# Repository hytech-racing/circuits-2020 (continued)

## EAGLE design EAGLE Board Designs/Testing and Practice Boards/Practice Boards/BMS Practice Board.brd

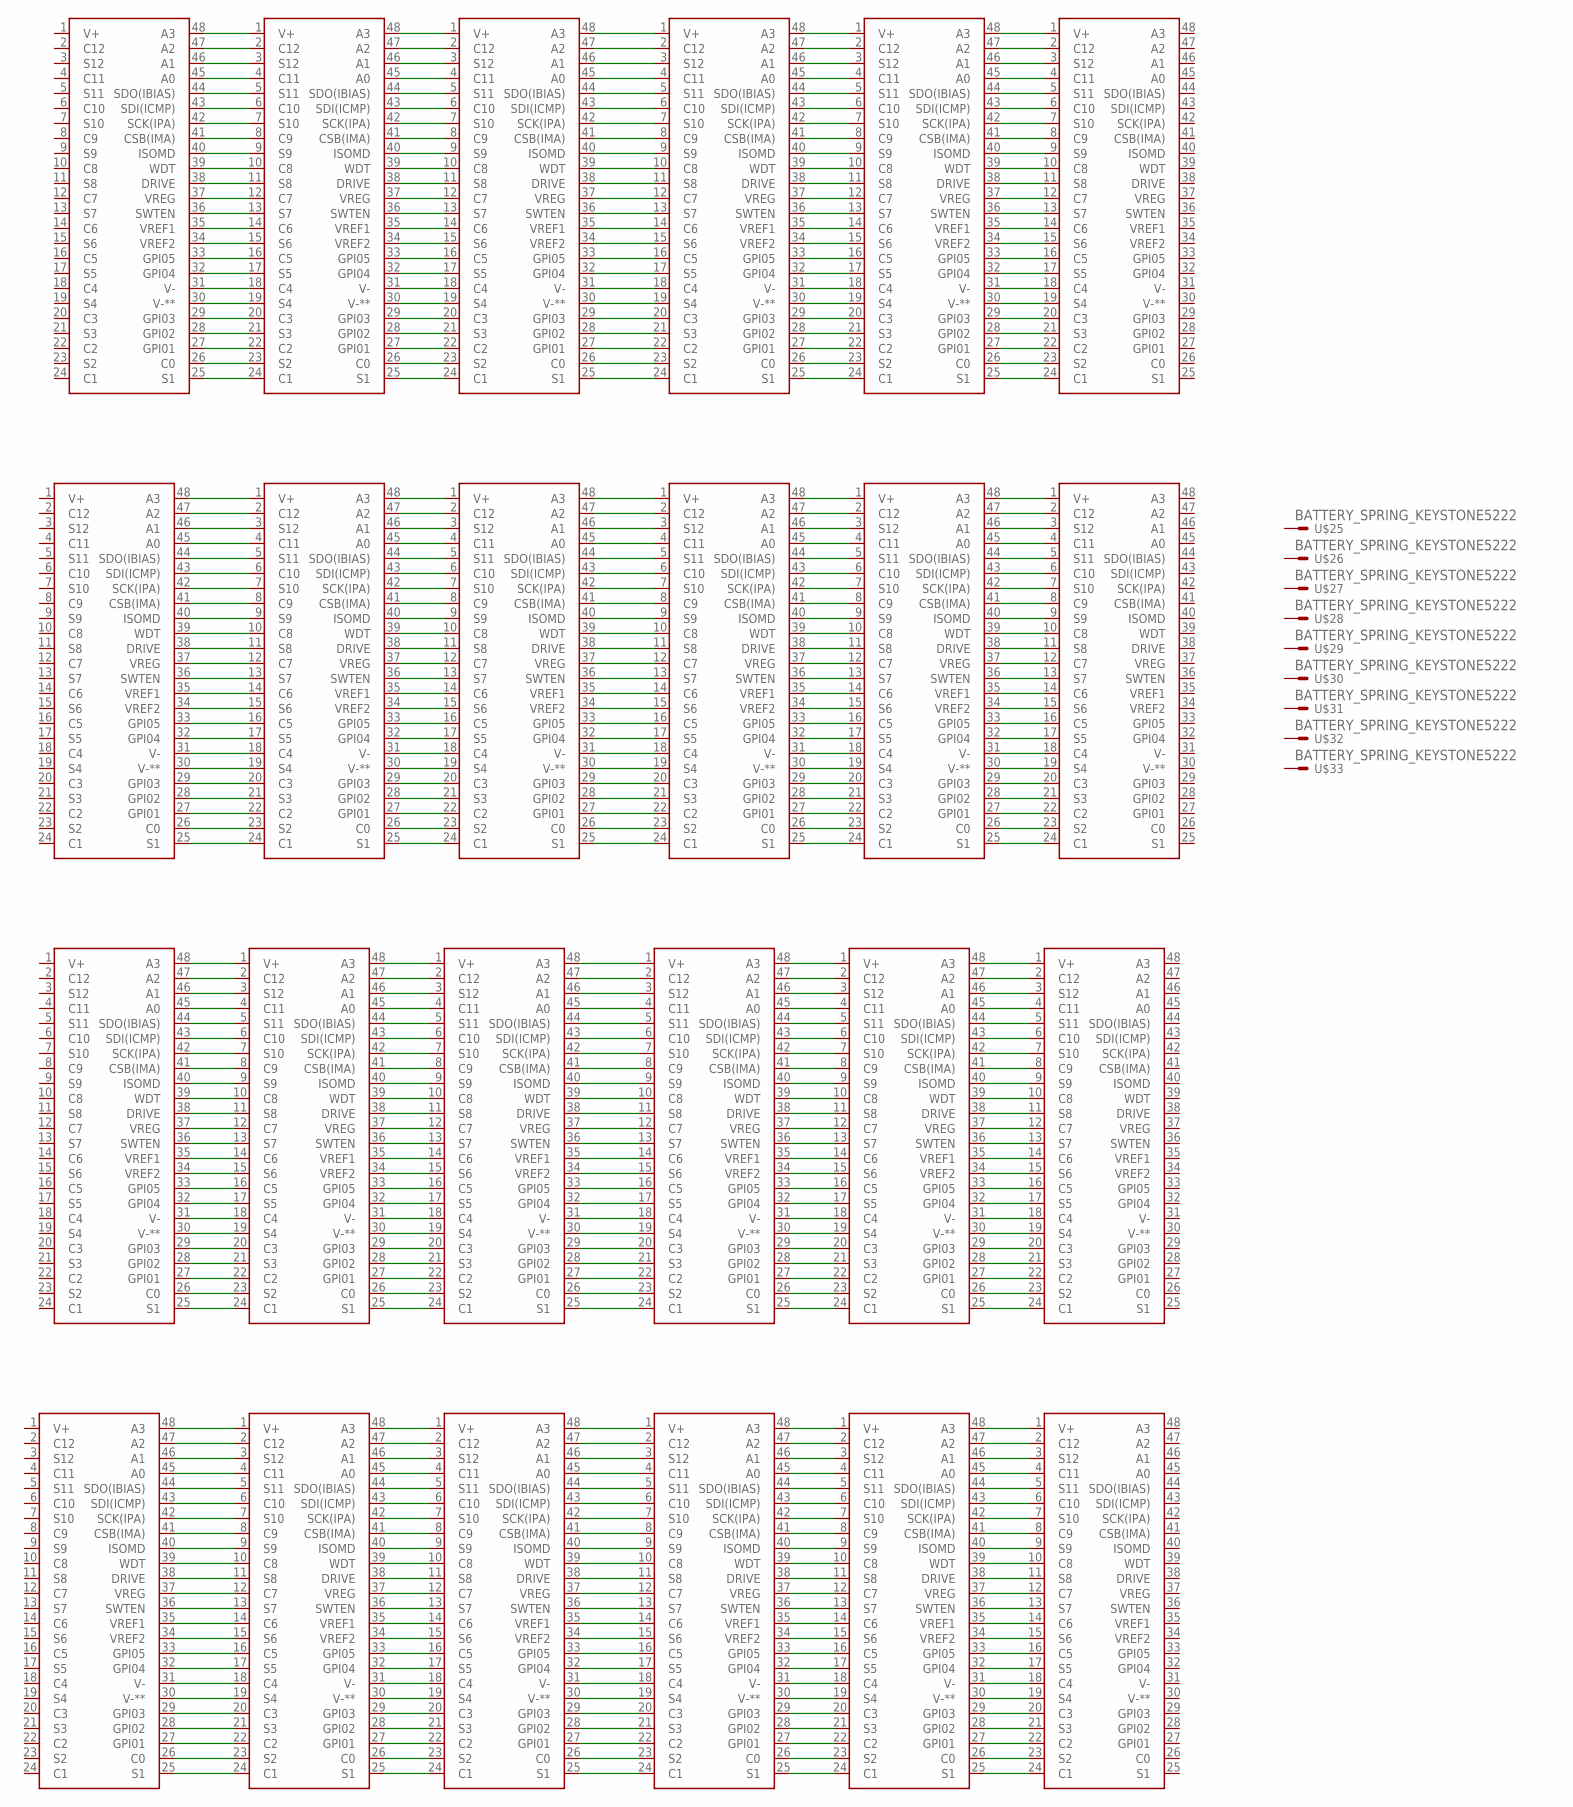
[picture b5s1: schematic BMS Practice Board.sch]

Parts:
U$1, U$2, U$3, U$4, U$5, U$6, U$7, U$8, U$9, U$10, U$11, U$12, U$13, U$14, U$15, U$16, U$17, U$18, U$19, U$20, U$21, U$22, U$23, U$24: LTC6804-2; LTC6804
U$25, U$26, U$27, U$28, U$29, U$30, U$31, U$32, U$33: BATTERY_SPRING_KEYSTONE5222; KEYSTONE5222

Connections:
unnamed: U$1.48 (A3), U$2.1 (V+)
unnamed: U$1.47 (A2), U$2.2 (C12)
unnamed: U$1.46 (A1), U$2.3 (S12)
unnamed: U$1.45 (A0), U$2.4 (C11)
unnamed: U$1.44 (SDO(IBIAS)), U$2.5 (S11)
unnamed: U$1.43 (SDI(ICMP)), U$2.6 (C10)
unnamed: U$1.42 (SCK(IPA)), U$2.7 (S10)
unnamed: U$1.41 (CSB(IMA)), U$2.8 (C9)
unnamed: U$1.40 (ISOMD), U$2.9 (S9)
unnamed: U$1.39 (WDT), U$2.10 (C8)
unnamed: U$1.38 (DRIVE), U$2.11 (S8)
unnamed: U$1.37 (VREG), U$2.12 (C7)
unnamed: U$1.36 (SWTEN), U$2.13 (S7)
unnamed: U$1.35 (VREF1), U$2.14 (C6)
unnamed: U$1.34 (VREF2), U$2.15 (S6)
unnamed: U$1.33 (GPI05), U$2.16 (C5)
unnamed: U$1.32 (GPI04), U$2.17 (S5)
unnamed: U$1.31 (V-), U$2.18 (C4)
unnamed: U$1.30 (V-**), U$2.19 (S4)
unnamed: U$1.29 (GPI03), U$2.20 (C3)
unnamed: U$1.28 (GPI02), U$2.21 (S3)
unnamed: U$1.27 (GPI01), U$2.22 (C2)
unnamed: U$1.26 (C0), U$2.23 (S2)
unnamed: U$1.25 (S1), U$2.24 (C1)
unnamed: U$2.48 (A3), U$3.1 (V+)
unnamed: U$2.47 (A2), U$3.2 (C12)
unnamed: U$2.46 (A1), U$3.3 (S12)
unnamed: U$2.45 (A0), U$3.4 (C11)
unnamed: U$2.44 (SDO(IBIAS)), U$3.5 (S11)
unnamed: U$2.43 (SDI(ICMP)), U$3.6 (C10)
unnamed: U$2.42 (SCK(IPA)), U$3.7 (S10)
unnamed: U$2.41 (CSB(IMA)), U$3.8 (C9)
unnamed: U$2.40 (ISOMD), U$3.9 (S9)
unnamed: U$2.39 (WDT), U$3.10 (C8)
unnamed: U$2.38 (DRIVE), U$3.11 (S8)
unnamed: U$2.37 (VREG), U$3.12 (C7)
unnamed: U$2.36 (SWTEN), U$3.13 (S7)
unnamed: U$2.35 (VREF1), U$3.14 (C6)
unnamed: U$2.34 (VREF2), U$3.15 (S6)
unnamed: U$2.33 (GPI05), U$3.16 (C5)
unnamed: U$2.32 (GPI04), U$3.17 (S5)
unnamed: U$2.31 (V-), U$3.18 (C4)
unnamed: U$2.30 (V-**), U$3.19 (S4)
unnamed: U$2.29 (GPI03), U$3.20 (C3)
unnamed: U$2.28 (GPI02), U$3.21 (S3)
unnamed: U$2.27 (GPI01), U$3.22 (C2)
unnamed: U$2.26 (C0), U$3.23 (S2)
unnamed: U$2.25 (S1), U$3.24 (C1)
unnamed: U$3.48 (A3), U$4.1 (V+)
unnamed: U$3.47 (A2), U$4.2 (C12)
unnamed: U$3.46 (A1), U$4.3 (S12)
unnamed: U$3.45 (A0), U$4.4 (C11)
unnamed: U$3.44 (SDO(IBIAS)), U$4.5 (S11)
unnamed: U$3.43 (SDI(ICMP)), U$4.6 (C10)
unnamed: U$3.42 (SCK(IPA)), U$4.7 (S10)
unnamed: U$3.41 (CSB(IMA)), U$4.8 (C9)
unnamed: U$3.40 (ISOMD), U$4.9 (S9)
unnamed: U$3.39 (WDT), U$4.10 (C8)
unnamed: U$3.38 (DRIVE), U$4.11 (S8)
unnamed: U$3.37 (VREG), U$4.12 (C7)
unnamed: U$3.36 (SWTEN), U$4.13 (S7)
unnamed: U$3.35 (VREF1), U$4.14 (C6)
unnamed: U$3.34 (VREF2), U$4.15 (S6)
unnamed: U$3.33 (GPI05), U$4.16 (C5)
unnamed: U$3.32 (GPI04), U$4.17 (S5)
unnamed: U$3.31 (V-), U$4.18 (C4)
unnamed: U$3.30 (V-**), U$4.19 (S4)
unnamed: U$3.29 (GPI03), U$4.20 (C3)
unnamed: U$3.28 (GPI02), U$4.21 (S3)
unnamed: U$3.27 (GPI01), U$4.22 (C2)
unnamed: U$3.26 (C0), U$4.23 (S2)
unnamed: U$3.25 (S1), U$4.24 (C1)
unnamed: U$4.48 (A3), U$5.1 (V+)
unnamed: U$4.47 (A2), U$5.2 (C12)
unnamed: U$4.46 (A1), U$5.3 (S12)
unnamed: U$4.45 (A0), U$5.4 (C11)
unnamed: U$4.44 (SDO(IBIAS)), U$5.5 (S11)
unnamed: U$4.43 (SDI(ICMP)), U$5.6 (C10)
unnamed: U$4.42 (SCK(IPA)), U$5.7 (S10)
unnamed: U$4.41 (CSB(IMA)), U$5.8 (C9)
unnamed: U$4.40 (ISOMD), U$5.9 (S9)
unnamed: U$4.39 (WDT), U$5.10 (C8)
unnamed: U$4.38 (DRIVE), U$5.11 (S8)
unnamed: U$4.37 (VREG), U$5.12 (C7)
unnamed: U$4.36 (SWTEN), U$5.13 (S7)
unnamed: U$4.35 (VREF1), U$5.14 (C6)
unnamed: U$4.34 (VREF2), U$5.15 (S6)
unnamed: U$4.33 (GPI05), U$5.16 (C5)
unnamed: U$4.32 (GPI04), U$5.17 (S5)
unnamed: U$4.31 (V-), U$5.18 (C4)
unnamed: U$4.30 (V-**), U$5.19 (S4)
unnamed: U$4.29 (GPI03), U$5.20 (C3)
unnamed: U$4.28 (GPI02), U$5.21 (S3)
unnamed: U$4.27 (GPI01), U$5.22 (C2)
unnamed: U$4.26 (C0), U$5.23 (S2)
unnamed: U$4.25 (S1), U$5.24 (C1)
unnamed: U$5.48 (A3), U$6.1 (V+)
unnamed: U$5.47 (A2), U$6.2 (C12)
unnamed: U$5.46 (A1), U$6.3 (S12)
unnamed: U$5.45 (A0), U$6.4 (C11)
unnamed: U$5.44 (SDO(IBIAS)), U$6.5 (S11)
unnamed: U$5.43 (SDI(ICMP)), U$6.6 (C10)
unnamed: U$5.42 (SCK(IPA)), U$6.7 (S10)
unnamed: U$5.41 (CSB(IMA)), U$6.8 (C9)
unnamed: U$5.40 (ISOMD), U$6.9 (S9)
unnamed: U$5.39 (WDT), U$6.10 (C8)
unnamed: U$5.38 (DRIVE), U$6.11 (S8)
unnamed: U$5.37 (VREG), U$6.12 (C7)
unnamed: U$5.36 (SWTEN), U$6.13 (S7)
unnamed: U$5.35 (VREF1), U$6.14 (C6)
unnamed: U$5.34 (VREF2), U$6.15 (S6)
unnamed: U$5.33 (GPI05), U$6.16 (C5)
unnamed: U$5.32 (GPI04), U$6.17 (S5)
unnamed: U$5.31 (V-), U$6.18 (C4)
unnamed: U$5.30 (V-**), U$6.19 (S4)
unnamed: U$5.29 (GPI03), U$6.20 (C3)
unnamed: U$5.28 (GPI02), U$6.21 (S3)
unnamed: U$5.27 (GPI01), U$6.22 (C2)
unnamed: U$5.26 (C0), U$6.23 (S2)
unnamed: U$5.25 (S1), U$6.24 (C1)
unnamed: U$7.25 (S1), U$8.24 (C1)
unnamed: U$7.26 (C0), U$8.23 (S2)
unnamed: U$7.27 (GPI01), U$8.22 (C2)
unnamed: U$7.28 (GPI02), U$8.21 (S3)
unnamed: U$7.29 (GPI03), U$8.20 (C3)
unnamed: U$7.30 (V-**), U$8.19 (S4)
unnamed: U$7.31 (V-), U$8.18 (C4)
unnamed: U$7.32 (GPI04), U$8.17 (S5)
unnamed: U$7.33 (GPI05), U$8.16 (C5)
unnamed: U$7.34 (VREF2), U$8.15 (S6)
unnamed: U$7.35 (VREF1), U$8.14 (C6)
unnamed: U$7.36 (SWTEN), U$8.13 (S7)
unnamed: U$7.37 (VREG), U$8.12 (C7)
unnamed: U$7.38 (DRIVE), U$8.11 (S8)
unnamed: U$7.39 (WDT), U$8.10 (C8)
unnamed: U$7.40 (ISOMD), U$8.9 (S9)
unnamed: U$7.41 (CSB(IMA)), U$8.8 (C9)
unnamed: U$7.42 (SCK(IPA)), U$8.7 (S10)
unnamed: U$7.43 (SDI(ICMP)), U$8.6 (C10)
unnamed: U$7.44 (SDO(IBIAS)), U$8.5 (S11)
unnamed: U$7.45 (A0), U$8.4 (C11)
unnamed: U$7.46 (A1), U$8.3 (S12)
unnamed: U$7.47 (A2), U$8.2 (C12)
unnamed: U$7.48 (A3), U$8.1 (V+)
unnamed: U$8.25 (S1), U$9.24 (C1)
unnamed: U$8.26 (C0), U$9.23 (S2)
unnamed: U$8.27 (GPI01), U$9.22 (C2)
unnamed: U$8.28 (GPI02), U$9.21 (S3)
unnamed: U$8.29 (GPI03), U$9.20 (C3)
unnamed: U$8.30 (V-**), U$9.19 (S4)
unnamed: U$8.31 (V-), U$9.18 (C4)
unnamed: U$8.32 (GPI04), U$9.17 (S5)
unnamed: U$8.33 (GPI05), U$9.16 (C5)
unnamed: U$8.34 (VREF2), U$9.15 (S6)
unnamed: U$8.35 (VREF1), U$9.14 (C6)
unnamed: U$8.36 (SWTEN), U$9.13 (S7)
unnamed: U$8.37 (VREG), U$9.12 (C7)
unnamed: U$8.38 (DRIVE), U$9.11 (S8)
unnamed: U$8.39 (WDT), U$9.10 (C8)
unnamed: U$8.40 (ISOMD), U$9.9 (S9)
unnamed: U$8.41 (CSB(IMA)), U$9.8 (C9)
unnamed: U$8.42 (SCK(IPA)), U$9.7 (S10)
unnamed: U$8.43 (SDI(ICMP)), U$9.6 (C10)
unnamed: U$8.44 (SDO(IBIAS)), U$9.5 (S11)
unnamed: U$8.45 (A0), U$9.4 (C11)
unnamed: U$8.46 (A1), U$9.3 (S12)
unnamed: U$8.47 (A2), U$9.2 (C12)
unnamed: U$8.48 (A3), U$9.1 (V+)
unnamed: U$9.25 (S1), U$10.24 (C1)
unnamed: U$9.26 (C0), U$10.23 (S2)
unnamed: U$9.27 (GPI01), U$10.22 (C2)
unnamed: U$9.28 (GPI02), U$10.21 (S3)
unnamed: U$9.29 (GPI03), U$10.20 (C3)
unnamed: U$9.30 (V-**), U$10.19 (S4)
unnamed: U$9.31 (V-), U$10.18 (C4)
unnamed: U$9.32 (GPI04), U$10.17 (S5)
unnamed: U$9.33 (GPI05), U$10.16 (C5)
unnamed: U$9.34 (VREF2), U$10.15 (S6)
unnamed: U$9.35 (VREF1), U$10.14 (C6)
unnamed: U$9.36 (SWTEN), U$10.13 (S7)
unnamed: U$9.37 (VREG), U$10.12 (C7)
unnamed: U$9.38 (DRIVE), U$10.11 (S8)
unnamed: U$9.39 (WDT), U$10.10 (C8)
unnamed: U$9.40 (ISOMD), U$10.9 (S9)
unnamed: U$9.41 (CSB(IMA)), U$10.8 (C9)
unnamed: U$9.42 (SCK(IPA)), U$10.7 (S10)
unnamed: U$9.43 (SDI(ICMP)), U$10.6 (C10)
unnamed: U$9.44 (SDO(IBIAS)), U$10.5 (S11)
unnamed: U$9.45 (A0), U$10.4 (C11)
unnamed: U$9.46 (A1), U$10.3 (S12)
unnamed: U$9.47 (A2), U$10.2 (C12)
unnamed: U$9.48 (A3), U$10.1 (V+)
unnamed: U$10.25 (S1), U$11.24 (C1)
unnamed: U$10.26 (C0), U$11.23 (S2)
unnamed: U$10.27 (GPI01), U$11.22 (C2)
unnamed: U$10.28 (GPI02), U$11.21 (S3)
unnamed: U$10.29 (GPI03), U$11.20 (C3)
unnamed: U$10.30 (V-**), U$11.19 (S4)
unnamed: U$10.31 (V-), U$11.18 (C4)
unnamed: U$10.32 (GPI04), U$11.17 (S5)
unnamed: U$10.33 (GPI05), U$11.16 (C5)
unnamed: U$10.34 (VREF2), U$11.15 (S6)
unnamed: U$10.35 (VREF1), U$11.14 (C6)
unnamed: U$10.36 (SWTEN), U$11.13 (S7)
unnamed: U$10.37 (VREG), U$11.12 (C7)
unnamed: U$10.38 (DRIVE), U$11.11 (S8)
unnamed: U$10.39 (WDT), U$11.10 (C8)
unnamed: U$10.40 (ISOMD), U$11.9 (S9)
unnamed: U$10.41 (CSB(IMA)), U$11.8 (C9)
unnamed: U$10.42 (SCK(IPA)), U$11.7 (S10)
unnamed: U$10.43 (SDI(ICMP)), U$11.6 (C10)
unnamed: U$10.44 (SDO(IBIAS)), U$11.5 (S11)
unnamed: U$10.45 (A0), U$11.4 (C11)
unnamed: U$10.46 (A1), U$11.3 (S12)
unnamed: U$10.47 (A2), U$11.2 (C12)
unnamed: U$10.48 (A3), U$11.1 (V+)
unnamed: U$11.25 (S1), U$12.24 (C1)
unnamed: U$11.26 (C0), U$12.23 (S2)
unnamed: U$11.27 (GPI01), U$12.22 (C2)
unnamed: U$11.28 (GPI02), U$12.21 (S3)
unnamed: U$11.29 (GPI03), U$12.20 (C3)
unnamed: U$11.30 (V-**), U$12.19 (S4)
unnamed: U$11.31 (V-), U$12.18 (C4)
unnamed: U$11.32 (GPI04), U$12.17 (S5)
unnamed: U$11.33 (GPI05), U$12.16 (C5)
unnamed: U$11.34 (VREF2), U$12.15 (S6)
unnamed: U$11.35 (VREF1), U$12.14 (C6)
unnamed: U$11.36 (SWTEN), U$12.13 (S7)
unnamed: U$11.37 (VREG), U$12.12 (C7)
unnamed: U$11.38 (DRIVE), U$12.11 (S8)
unnamed: U$11.39 (WDT), U$12.10 (C8)
unnamed: U$11.40 (ISOMD), U$12.9 (S9)
unnamed: U$11.41 (CSB(IMA)), U$12.8 (C9)
unnamed: U$11.42 (SCK(IPA)), U$12.7 (S10)
unnamed: U$11.43 (SDI(ICMP)), U$12.6 (C10)
unnamed: U$11.44 (SDO(IBIAS)), U$12.5 (S11)
unnamed: U$11.45 (A0), U$12.4 (C11)
unnamed: U$11.46 (A1), U$12.3 (S12)
unnamed: U$11.47 (A2), U$12.2 (C12)
unnamed: U$11.48 (A3), U$12.1 (V+)
unnamed: U$13.48 (A3), U$14.1 (V+)
unnamed: U$13.47 (A2), U$14.2 (C12)
unnamed: U$13.46 (A1), U$14.3 (S12)
unnamed: U$13.45 (A0), U$14.4 (C11)
unnamed: U$13.44 (SDO(IBIAS)), U$14.5 (S11)
unnamed: U$13.43 (SDI(ICMP)), U$14.6 (C10)
unnamed: U$13.42 (SCK(IPA)), U$14.7 (S10)
unnamed: U$13.41 (CSB(IMA)), U$14.8 (C9)
unnamed: U$13.40 (ISOMD), U$14.9 (S9)
unnamed: U$13.39 (WDT), U$14.10 (C8)
unnamed: U$13.38 (DRIVE), U$14.11 (S8)
unnamed: U$13.37 (VREG), U$14.12 (C7)
unnamed: U$13.36 (SWTEN), U$14.13 (S7)
unnamed: U$13.35 (VREF1), U$14.14 (C6)
unnamed: U$13.34 (VREF2), U$14.15 (S6)
unnamed: U$13.33 (GPI05), U$14.16 (C5)
unnamed: U$13.32 (GPI04), U$14.17 (S5)
unnamed: U$13.31 (V-), U$14.18 (C4)
unnamed: U$13.30 (V-**), U$14.19 (S4)
unnamed: U$13.29 (GPI03), U$14.20 (C3)
unnamed: U$13.28 (GPI02), U$14.21 (S3)
unnamed: U$13.27 (GPI01), U$14.22 (C2)
unnamed: U$13.26 (C0), U$14.23 (S2)
unnamed: U$13.25 (S1), U$14.24 (C1)
unnamed: U$14.48 (A3), U$15.1 (V+)
unnamed: U$14.47 (A2), U$15.2 (C12)
unnamed: U$14.46 (A1), U$15.3 (S12)
unnamed: U$14.45 (A0), U$15.4 (C11)
unnamed: U$14.44 (SDO(IBIAS)), U$15.5 (S11)
unnamed: U$14.43 (SDI(ICMP)), U$15.6 (C10)
unnamed: U$14.42 (SCK(IPA)), U$15.7 (S10)
unnamed: U$14.41 (CSB(IMA)), U$15.8 (C9)
unnamed: U$14.40 (ISOMD), U$15.9 (S9)
unnamed: U$14.39 (WDT), U$15.10 (C8)
unnamed: U$14.38 (DRIVE), U$15.11 (S8)
unnamed: U$14.37 (VREG), U$15.12 (C7)
unnamed: U$14.36 (SWTEN), U$15.13 (S7)
unnamed: U$14.35 (VREF1), U$15.14 (C6)
unnamed: U$14.34 (VREF2), U$15.15 (S6)
unnamed: U$14.33 (GPI05), U$15.16 (C5)
unnamed: U$14.32 (GPI04), U$15.17 (S5)
unnamed: U$14.31 (V-), U$15.18 (C4)
unnamed: U$14.30 (V-**), U$15.19 (S4)
unnamed: U$14.29 (GPI03), U$15.20 (C3)
unnamed: U$14.28 (GPI02), U$15.21 (S3)
unnamed: U$14.27 (GPI01), U$15.22 (C2)
unnamed: U$14.26 (C0), U$15.23 (S2)
unnamed: U$14.25 (S1), U$15.24 (C1)
unnamed: U$15.48 (A3), U$16.1 (V+)
unnamed: U$15.47 (A2), U$16.2 (C12)
unnamed: U$15.46 (A1), U$16.3 (S12)
unnamed: U$15.45 (A0), U$16.4 (C11)
unnamed: U$15.44 (SDO(IBIAS)), U$16.5 (S11)
unnamed: U$15.43 (SDI(ICMP)), U$16.6 (C10)
unnamed: U$15.42 (SCK(IPA)), U$16.7 (S10)
unnamed: U$15.41 (CSB(IMA)), U$16.8 (C9)
unnamed: U$15.40 (ISOMD), U$16.9 (S9)
unnamed: U$15.39 (WDT), U$16.10 (C8)
unnamed: U$15.38 (DRIVE), U$16.11 (S8)
unnamed: U$15.37 (VREG), U$16.12 (C7)
unnamed: U$15.36 (SWTEN), U$16.13 (S7)
unnamed: U$15.35 (VREF1), U$16.14 (C6)
unnamed: U$15.34 (VREF2), U$16.15 (S6)
unnamed: U$15.33 (GPI05), U$16.16 (C5)
unnamed: U$15.32 (GPI04), U$16.17 (S5)
unnamed: U$15.31 (V-), U$16.18 (C4)
unnamed: U$15.30 (V-**), U$16.19 (S4)
unnamed: U$15.29 (GPI03), U$16.20 (C3)
unnamed: U$15.28 (GPI02), U$16.21 (S3)
unnamed: U$15.27 (GPI01), U$16.22 (C2)
unnamed: U$15.26 (C0), U$16.23 (S2)
unnamed: U$15.25 (S1), U$16.24 (C1)
unnamed: U$16.48 (A3), U$17.1 (V+)
unnamed: U$16.47 (A2), U$17.2 (C12)
unnamed: U$16.46 (A1), U$17.3 (S12)
unnamed: U$16.45 (A0), U$17.4 (C11)
unnamed: U$16.44 (SDO(IBIAS)), U$17.5 (S11)
unnamed: U$16.43 (SDI(ICMP)), U$17.6 (C10)
unnamed: U$16.42 (SCK(IPA)), U$17.7 (S10)
unnamed: U$16.41 (CSB(IMA)), U$17.8 (C9)
unnamed: U$16.40 (ISOMD), U$17.9 (S9)
unnamed: U$16.39 (WDT), U$17.10 (C8)
unnamed: U$16.38 (DRIVE), U$17.11 (S8)
unnamed: U$16.37 (VREG), U$17.12 (C7)
unnamed: U$16.36 (SWTEN), U$17.13 (S7)
unnamed: U$16.35 (VREF1), U$17.14 (C6)
unnamed: U$16.34 (VREF2), U$17.15 (S6)
unnamed: U$16.33 (GPI05), U$17.16 (C5)
unnamed: U$16.32 (GPI04), U$17.17 (S5)
unnamed: U$16.31 (V-), U$17.18 (C4)
unnamed: U$16.30 (V-**), U$17.19 (S4)
unnamed: U$16.29 (GPI03), U$17.20 (C3)
unnamed: U$16.28 (GPI02), U$17.21 (S3)
unnamed: U$16.27 (GPI01), U$17.22 (C2)
unnamed: U$16.26 (C0), U$17.23 (S2)
unnamed: U$16.25 (S1), U$17.24 (C1)
unnamed: U$17.48 (A3), U$18.1 (V+)
unnamed: U$17.47 (A2), U$18.2 (C12)
unnamed: U$17.46 (A1), U$18.3 (S12)
unnamed: U$17.45 (A0), U$18.4 (C11)
unnamed: U$17.44 (SDO(IBIAS)), U$18.5 (S11)
unnamed: U$17.43 (SDI(ICMP)), U$18.6 (C10)
unnamed: U$17.42 (SCK(IPA)), U$18.7 (S10)
unnamed: U$17.41 (CSB(IMA)), U$18.8 (C9)
unnamed: U$17.40 (ISOMD), U$18.9 (S9)
unnamed: U$17.39 (WDT), U$18.10 (C8)
unnamed: U$17.38 (DRIVE), U$18.11 (S8)
unnamed: U$17.37 (VREG), U$18.12 (C7)
unnamed: U$17.36 (SWTEN), U$18.13 (S7)
unnamed: U$17.35 (VREF1), U$18.14 (C6)
unnamed: U$17.34 (VREF2), U$18.15 (S6)
unnamed: U$17.33 (GPI05), U$18.16 (C5)
unnamed: U$17.32 (GPI04), U$18.17 (S5)
unnamed: U$17.31 (V-), U$18.18 (C4)
unnamed: U$17.30 (V-**), U$18.19 (S4)
unnamed: U$17.29 (GPI03), U$18.20 (C3)
unnamed: U$17.28 (GPI02), U$18.21 (S3)
unnamed: U$17.27 (GPI01), U$18.22 (C2)
unnamed: U$17.26 (C0), U$18.23 (S2)
unnamed: U$17.25 (S1), U$18.24 (C1)
unnamed: U$19.25 (S1), U$20.24 (C1)
unnamed: U$19.26 (C0), U$20.23 (S2)
unnamed: U$19.27 (GPI01), U$20.22 (C2)
unnamed: U$19.28 (GPI02), U$20.21 (S3)
unnamed: U$19.29 (GPI03), U$20.20 (C3)
unnamed: U$19.30 (V-**), U$20.19 (S4)
unnamed: U$19.31 (V-), U$20.18 (C4)
unnamed: U$19.32 (GPI04), U$20.17 (S5)
unnamed: U$19.33 (GPI05), U$20.16 (C5)
unnamed: U$19.34 (VREF2), U$20.15 (S6)
unnamed: U$19.35 (VREF1), U$20.14 (C6)
unnamed: U$19.36 (SWTEN), U$20.13 (S7)
unnamed: U$19.37 (VREG), U$20.12 (C7)
unnamed: U$19.38 (DRIVE), U$20.11 (S8)
unnamed: U$19.39 (WDT), U$20.10 (C8)
unnamed: U$19.40 (ISOMD), U$20.9 (S9)
unnamed: U$19.41 (CSB(IMA)), U$20.8 (C9)
unnamed: U$19.42 (SCK(IPA)), U$20.7 (S10)
unnamed: U$19.43 (SDI(ICMP)), U$20.6 (C10)
unnamed: U$19.44 (SDO(IBIAS)), U$20.5 (S11)
unnamed: U$19.45 (A0), U$20.4 (C11)
unnamed: U$19.46 (A1), U$20.3 (S12)
unnamed: U$19.47 (A2), U$20.2 (C12)
unnamed: U$19.48 (A3), U$20.1 (V+)
unnamed: U$20.25 (S1), U$21.24 (C1)
unnamed: U$20.26 (C0), U$21.23 (S2)
unnamed: U$20.27 (GPI01), U$21.22 (C2)
unnamed: U$20.28 (GPI02), U$21.21 (S3)
unnamed: U$20.29 (GPI03), U$21.20 (C3)
unnamed: U$20.30 (V-**), U$21.19 (S4)
unnamed: U$20.31 (V-), U$21.18 (C4)
unnamed: U$20.32 (GPI04), U$21.17 (S5)
unnamed: U$20.33 (GPI05), U$21.16 (C5)
unnamed: U$20.34 (VREF2), U$21.15 (S6)
unnamed: U$20.35 (VREF1), U$21.14 (C6)
unnamed: U$20.36 (SWTEN), U$21.13 (S7)
unnamed: U$20.37 (VREG), U$21.12 (C7)
unnamed: U$20.38 (DRIVE), U$21.11 (S8)
unnamed: U$20.39 (WDT), U$21.10 (C8)
unnamed: U$20.40 (ISOMD), U$21.9 (S9)
unnamed: U$20.41 (CSB(IMA)), U$21.8 (C9)
unnamed: U$20.42 (SCK(IPA)), U$21.7 (S10)
unnamed: U$20.43 (SDI(ICMP)), U$21.6 (C10)
unnamed: U$20.44 (SDO(IBIAS)), U$21.5 (S11)
unnamed: U$20.45 (A0), U$21.4 (C11)
unnamed: U$20.46 (A1), U$21.3 (S12)
unnamed: U$20.47 (A2), U$21.2 (C12)
unnamed: U$20.48 (A3), U$21.1 (V+)
unnamed: U$21.25 (S1), U$22.24 (C1)
unnamed: U$21.26 (C0), U$22.23 (S2)
unnamed: U$21.27 (GPI01), U$22.22 (C2)
unnamed: U$21.28 (GPI02), U$22.21 (S3)
unnamed: U$21.29 (GPI03), U$22.20 (C3)
unnamed: U$21.30 (V-**), U$22.19 (S4)
unnamed: U$21.31 (V-), U$22.18 (C4)
unnamed: U$21.32 (GPI04), U$22.17 (S5)
unnamed: U$21.33 (GPI05), U$22.16 (C5)
unnamed: U$21.34 (VREF2), U$22.15 (S6)
unnamed: U$21.35 (VREF1), U$22.14 (C6)
unnamed: U$21.36 (SWTEN), U$22.13 (S7)
unnamed: U$21.37 (VREG), U$22.12 (C7)
unnamed: U$21.38 (DRIVE), U$22.11 (S8)
unnamed: U$21.39 (WDT), U$22.10 (C8)
unnamed: U$21.40 (ISOMD), U$22.9 (S9)
unnamed: U$21.41 (CSB(IMA)), U$22.8 (C9)
unnamed: U$21.42 (SCK(IPA)), U$22.7 (S10)
unnamed: U$21.43 (SDI(ICMP)), U$22.6 (C10)
unnamed: U$21.44 (SDO(IBIAS)), U$22.5 (S11)
unnamed: U$21.45 (A0), U$22.4 (C11)
unnamed: U$21.46 (A1), U$22.3 (S12)
unnamed: U$21.47 (A2), U$22.2 (C12)
unnamed: U$21.48 (A3), U$22.1 (V+)
unnamed: U$22.25 (S1), U$23.24 (C1)
unnamed: U$22.26 (C0), U$23.23 (S2)
unnamed: U$22.27 (GPI01), U$23.22 (C2)
unnamed: U$22.28 (GPI02), U$23.21 (S3)
unnamed: U$22.29 (GPI03), U$23.20 (C3)
unnamed: U$22.30 (V-**), U$23.19 (S4)
unnamed: U$22.31 (V-), U$23.18 (C4)
unnamed: U$22.32 (GPI04), U$23.17 (S5)
unnamed: U$22.33 (GPI05), U$23.16 (C5)
unnamed: U$22.34 (VREF2), U$23.15 (S6)
unnamed: U$22.35 (VREF1), U$23.14 (C6)
unnamed: U$22.36 (SWTEN), U$23.13 (S7)
unnamed: U$22.37 (VREG), U$23.12 (C7)
unnamed: U$22.38 (DRIVE), U$23.11 (S8)
unnamed: U$22.39 (WDT), U$23.10 (C8)
unnamed: U$22.40 (ISOMD), U$23.9 (S9)
unnamed: U$22.41 (CSB(IMA)), U$23.8 (C9)
unnamed: U$22.42 (SCK(IPA)), U$23.7 (S10)
unnamed: U$22.43 (SDI(ICMP)), U$23.6 (C10)
unnamed: U$22.44 (SDO(IBIAS)), U$23.5 (S11)
unnamed: U$22.45 (A0), U$23.4 (C11)
unnamed: U$22.46 (A1), U$23.3 (S12)
unnamed: U$22.47 (A2), U$23.2 (C12)
unnamed: U$22.48 (A3), U$23.1 (V+)
unnamed: U$23.25 (S1), U$24.24 (C1)
unnamed: U$23.26 (C0), U$24.23 (S2)
unnamed: U$23.27 (GPI01), U$24.22 (C2)
unnamed: U$23.28 (GPI02), U$24.21 (S3)
unnamed: U$23.29 (GPI03), U$24.20 (C3)
unnamed: U$23.30 (V-**), U$24.19 (S4)
unnamed: U$23.31 (V-), U$24.18 (C4)
unnamed: U$23.32 (GPI04), U$24.17 (S5)
unnamed: U$23.33 (GPI05), U$24.16 (C5)
unnamed: U$23.34 (VREF2), U$24.15 (S6)
unnamed: U$23.35 (VREF1), U$24.14 (C6)
unnamed: U$23.36 (SWTEN), U$24.13 (S7)
unnamed: U$23.37 (VREG), U$24.12 (C7)
unnamed: U$23.38 (DRIVE), U$24.11 (S8)
unnamed: U$23.39 (WDT), U$24.10 (C8)
unnamed: U$23.40 (ISOMD), U$24.9 (S9)
unnamed: U$23.41 (CSB(IMA)), U$24.8 (C9)
unnamed: U$23.42 (SCK(IPA)), U$24.7 (S10)
unnamed: U$23.43 (SDI(ICMP)), U$24.6 (C10)
unnamed: U$23.44 (SDO(IBIAS)), U$24.5 (S11)
unnamed: U$23.45 (A0), U$24.4 (C11)
unnamed: U$23.46 (A1), U$24.3 (S12)
unnamed: U$23.47 (A2), U$24.2 (C12)
unnamed: U$23.48 (A3), U$24.1 (V+)

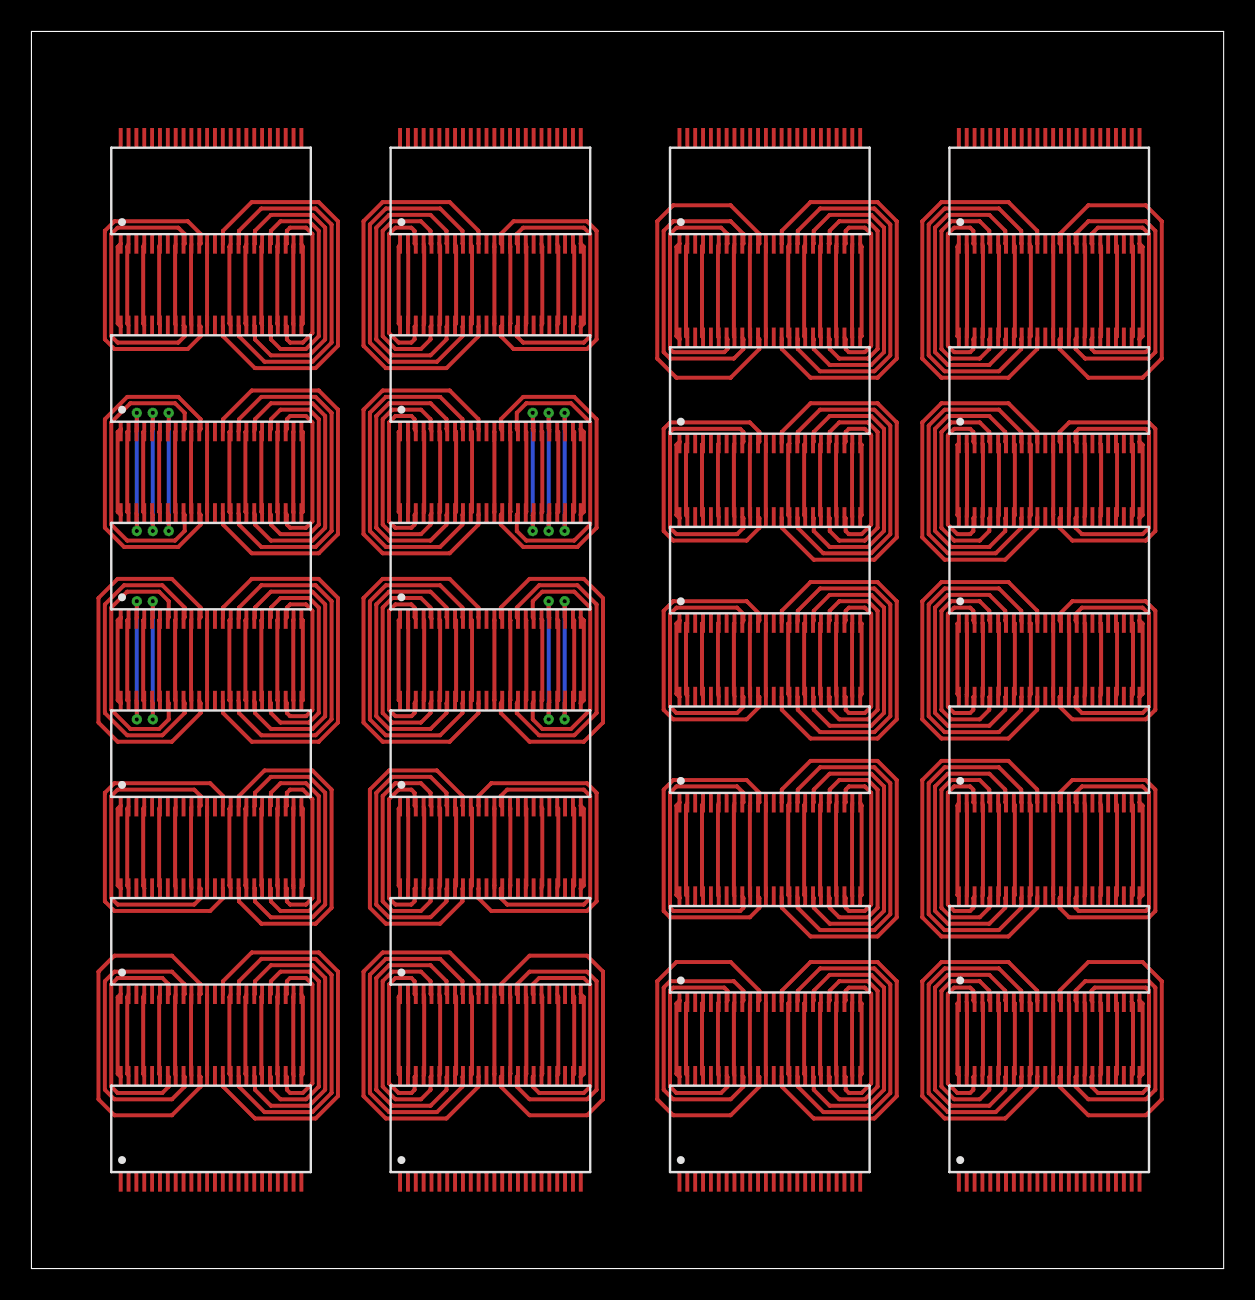
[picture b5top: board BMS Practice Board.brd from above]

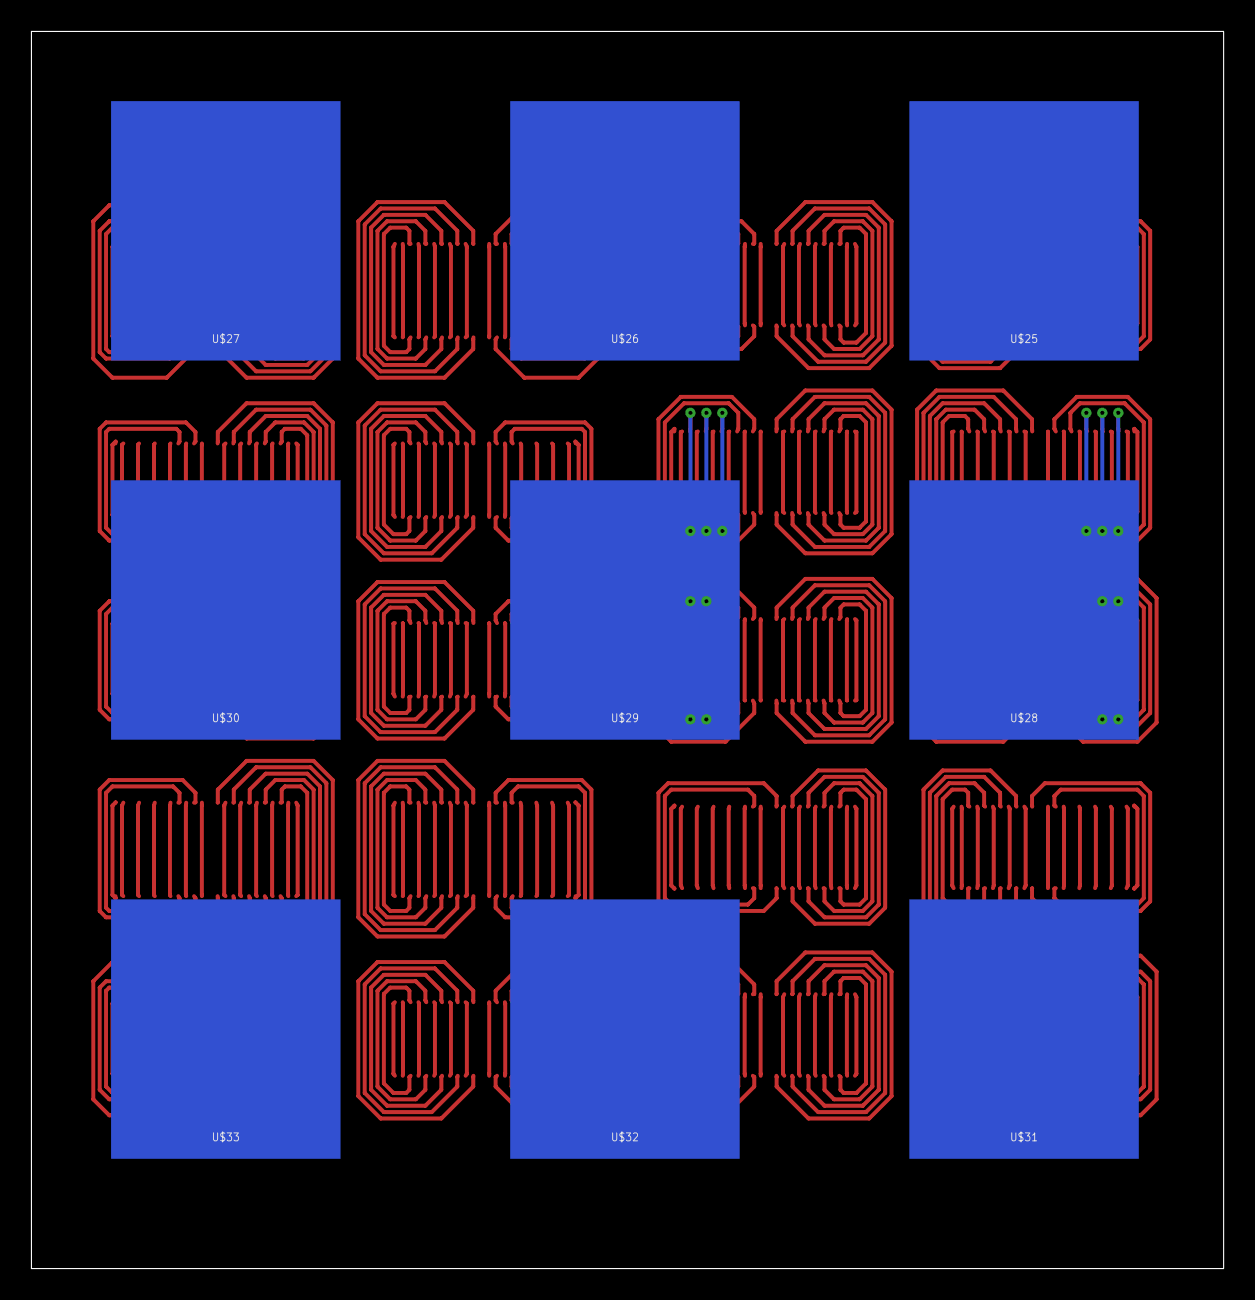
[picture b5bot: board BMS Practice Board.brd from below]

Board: 2 copper layers, 75.9 x 78.7 mm, 33 parts (9 on the bottom side), 480 nets.

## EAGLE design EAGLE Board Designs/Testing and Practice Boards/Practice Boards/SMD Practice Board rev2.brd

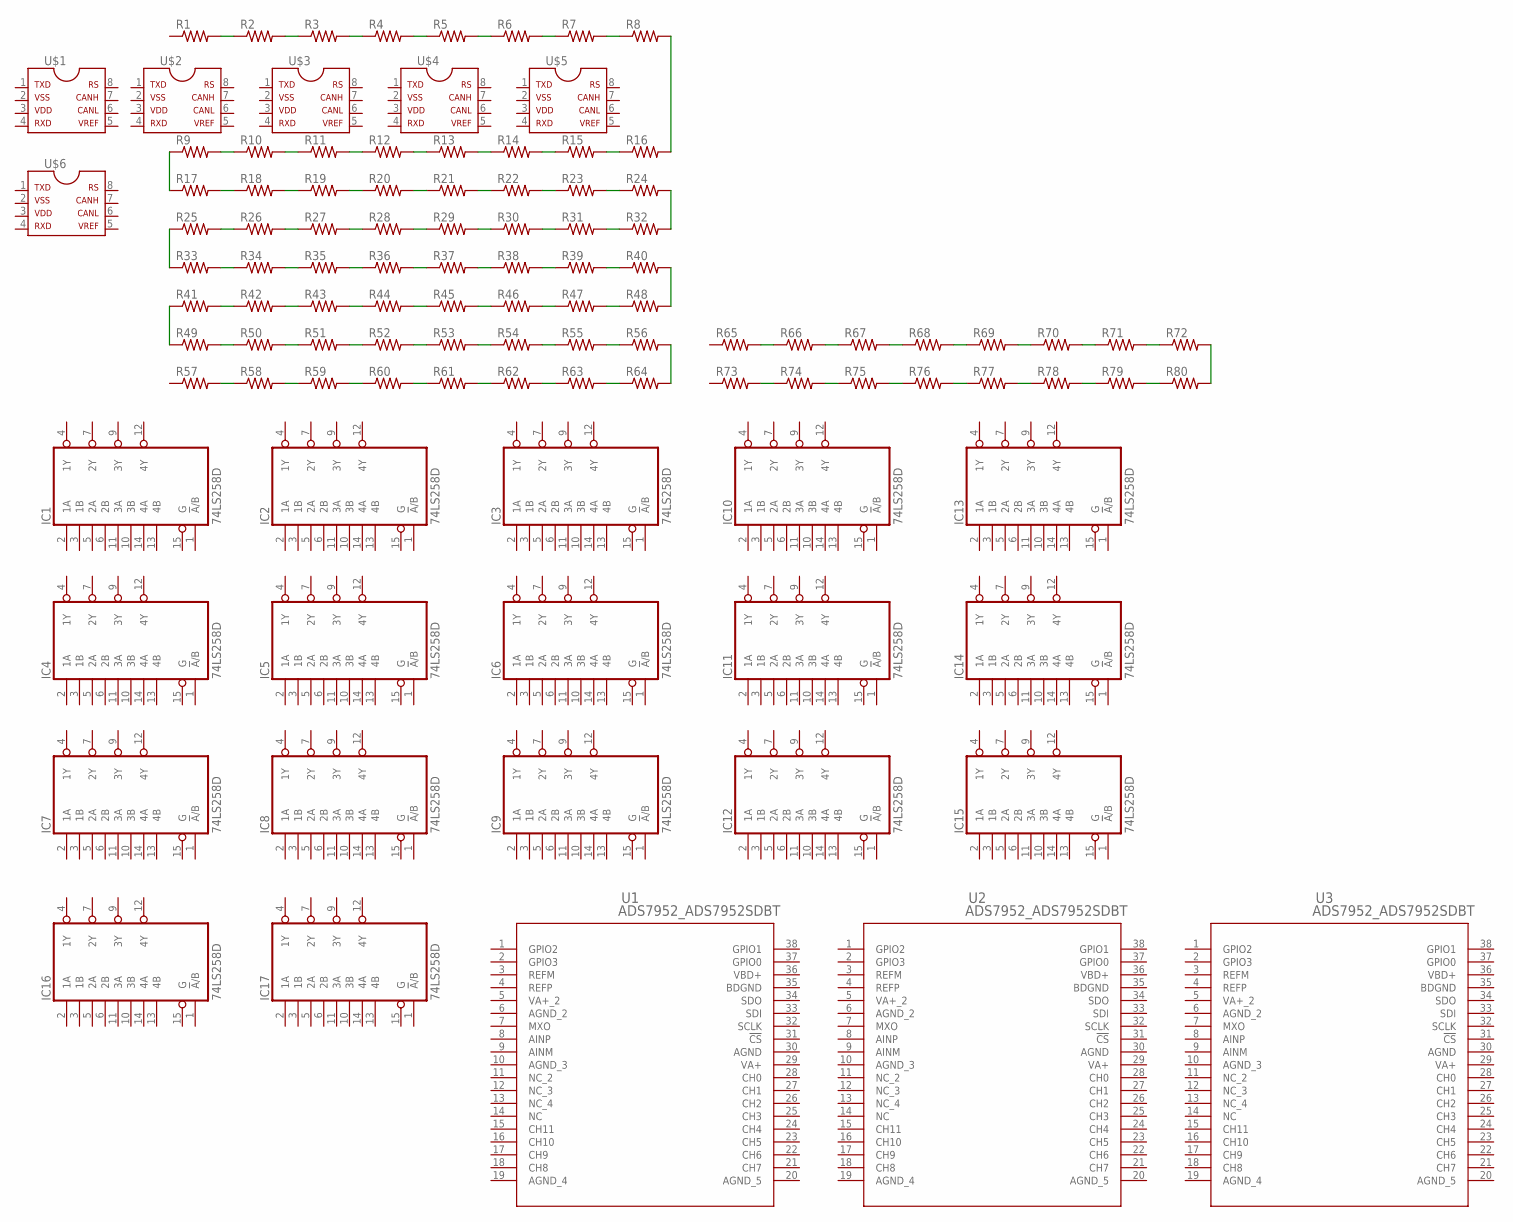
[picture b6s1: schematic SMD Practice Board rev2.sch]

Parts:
IC1, IC2, IC3, IC4, IC5, IC6, IC7, IC8, IC9, IC10, IC11, IC12, IC13, IC14, IC15, IC16, IC17: 74LS258D; SO16
R1, R2, R3, R4, R5, R6, R7, R8, R9, R10, R11, R12, R13, R14, R15, R16, R17, R18, R19, R20, R21, R22, R23, R24, R25, R26, R27, R28, R29, R30, R31, R32, R33, R34, R35, R36, R37, R38, R39, R40, R41, R42, R43, R44, R45, R46, R47, R48, R49, R50, R51, R52, R53, R54, R55, R56, R57, R58, R59, R60, R61, R62, R63, R64, R65, R66, R67, R68, R69, R70, R71, R72, R73, R74, R75, R76, R77, R78, R79, R80: RESISTOR0805-RES; 0805
U1, U2, U3: ADS7952_ADS7952SDBT; ADS7952_DBT38
U$1, U$2, U$3, U$4, U$5, U$6: MCP2551; SOIC-08

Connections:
AGND: U1.30 (AGND), U2.30 (AGND), U3.30 (AGND)
AGND_2: U1.6 (AGND_2), U2.6 (AGND_2), U3.6 (AGND_2)
AGND_3: U1.10 (AGND_3), U2.10 (AGND_3), U3.10 (AGND_3)
AGND_4: U1.19 (AGND_4), U2.19 (AGND_4), U3.19 (AGND_4)
AGND_5: U1.20 (AGND_5), U2.20 (AGND_5), U3.20 (AGND_5)
BDGND: U1.35 (BDGND), U2.35 (BDGND), U3.35 (BDGND)
GND: IC1.8 (GND), IC2.8 (GND), IC3.8 (GND), IC4.8 (GND), IC5.8 (GND), IC6.8 (GND), IC7.8 (GND), IC8.8 (GND), IC9.8 (GND), IC10.8 (GND), IC11.8 (GND), IC12.8 (GND), IC13.8 (GND), IC14.8 (GND), IC15.8 (GND), IC16.8 (GND), IC17.8 (GND)
unnamed: R1.2, R2.1
unnamed: R2.2, R3.1
unnamed: R3.2, R4.1
unnamed: R5.2, R6.1
unnamed: R6.2, R7.1
unnamed: R7.2, R8.1
unnamed: R4.2, R5.1
unnamed: R9.2, R10.1
unnamed: R10.2, R11.1
unnamed: R11.2, R12.1
unnamed: R13.2, R14.1
unnamed: R14.2, R15.1
unnamed: R15.2, R16.1
unnamed: R12.2, R13.1
unnamed: R8.2, R16.2
unnamed: R17.2, R18.1
unnamed: R18.2, R19.1
unnamed: R19.2, R20.1
unnamed: R21.2, R22.1
unnamed: R22.2, R23.1
unnamed: R23.2, R24.1
unnamed: R20.2, R21.1
unnamed: R25.2, R26.1
unnamed: R26.2, R27.1
unnamed: R27.2, R28.1
unnamed: R29.2, R30.1
unnamed: R30.2, R31.1
unnamed: R31.2, R32.1
unnamed: R28.2, R29.1
unnamed: R24.2, R32.2
unnamed: R9.1, R17.1
unnamed: R33.2, R34.1
unnamed: R34.2, R35.1
unnamed: R35.2, R36.1
unnamed: R37.2, R38.1
unnamed: R38.2, R39.1
unnamed: R39.2, R40.1
unnamed: R36.2, R37.1
unnamed: R41.2, R42.1
unnamed: R42.2, R43.1
unnamed: R43.2, R44.1
unnamed: R45.2, R46.1
unnamed: R46.2, R47.1
unnamed: R47.2, R48.1
unnamed: R44.2, R45.1
unnamed: R40.2, R48.2
unnamed: R49.2, R50.1
unnamed: R50.2, R51.1
unnamed: R51.2, R52.1
unnamed: R53.2, R54.1
unnamed: R54.2, R55.1
unnamed: R55.2, R56.1
unnamed: R52.2, R53.1
unnamed: R57.2, R58.1
unnamed: R58.2, R59.1
unnamed: R59.2, R60.1
unnamed: R61.2, R62.1
unnamed: R62.2, R63.1
unnamed: R63.2, R64.1
unnamed: R60.2, R61.1
unnamed: R56.2, R64.2
unnamed: R41.1, R49.1
unnamed: R25.1, R33.1
unnamed: R65.2, R66.1
unnamed: R66.2, R67.1
unnamed: R67.2, R68.1
unnamed: R69.2, R70.1
unnamed: R70.2, R71.1
unnamed: R71.2, R72.1
unnamed: R68.2, R69.1
unnamed: R73.2, R74.1
unnamed: R74.2, R75.1
unnamed: R75.2, R76.1
unnamed: R77.2, R78.1
unnamed: R78.2, R79.1
unnamed: R79.2, R80.1
unnamed: R76.2, R77.1
unnamed: R72.2, R80.2
VA+: U1.29 (VA+), U2.29 (VA+), U3.29 (VA+)
VA+_2: U1.5 (VA+_2), U2.5 (VA+_2), U3.5 (VA+_2)
VBD+: U1.36 (VBD+), U2.36 (VBD+), U3.36 (VBD+)
VCC: IC1.16 (VCC), IC2.16 (VCC), IC3.16 (VCC), IC4.16 (VCC), IC5.16 (VCC), IC6.16 (VCC), IC7.16 (VCC), IC8.16 (VCC), IC9.16 (VCC), IC10.16 (VCC), IC11.16 (VCC), IC12.16 (VCC), IC13.16 (VCC), IC14.16 (VCC), IC15.16 (VCC), IC16.16 (VCC), IC17.16 (VCC)

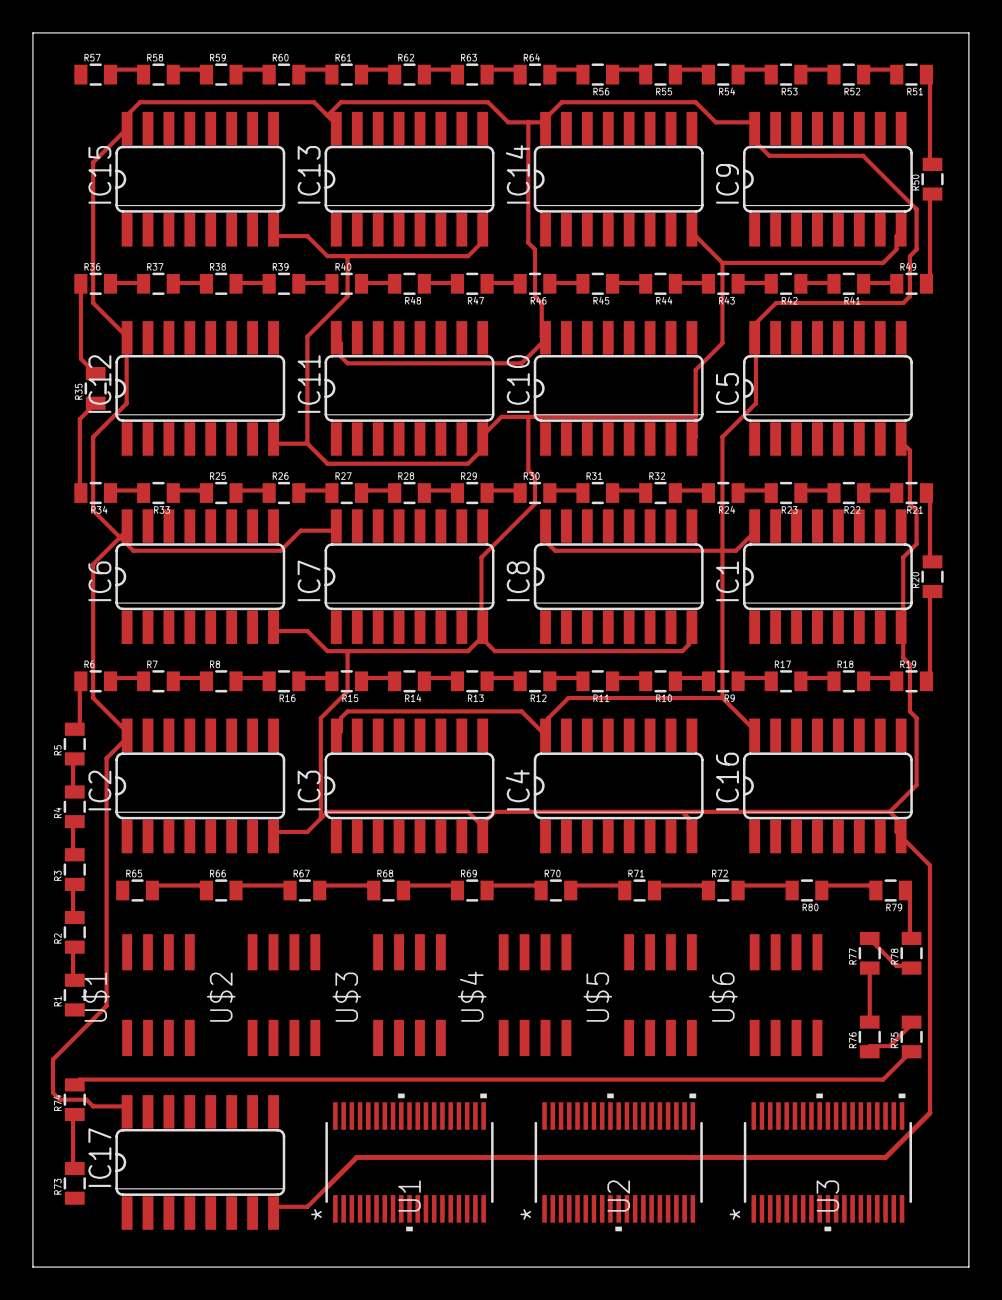
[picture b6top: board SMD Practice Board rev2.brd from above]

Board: 2 copper layers, 56.8 x 74.9 mm, 106 parts (0 on the bottom side), 89 nets.
